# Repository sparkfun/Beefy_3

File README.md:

SparkFun FTDI Basic Breakout Board-3.3V
========================================

[*SparkFun Beefy 3 (3.3V FTDI Breakout) (DEV-13746)*](https://www.sparkfun.com/products/13746)

This is a breakout board for the FTDI FT232RL USB to serial IC with integrated 3.3V (up to 600mA) regulator to power your project.
The pinout of this board matches the FTDI cable to work with official Arduino and cloned 3.3V Arduino boards.

Repository Contents
-------------------
* **/Hardware** &mdash; All Eagle design files (.brd, .sch)
* **/Production** &mdash; Test bed files and production panel files

Product Versions
----------------
* 
[This](https://www.sparkfun.com/products/13746) &mdash; Higher power 3.3V FTDI Breakout.
* [DEV-09873](https://www.sparkfun.com/products/9873) &mdash; 3.3V FTDI Basic Breakout.
* [DEV-09716](https://www.sparkfun.com/products/9716) &mdash; 5V FTDI Basic Breakout

License Information
-------------------
The hardware is released under [Creative Commons ShareAlike 4.0 International](https://creativecommons.org/licenses/by-sa/4.0/).

Distributed as-is; no warranty is given.

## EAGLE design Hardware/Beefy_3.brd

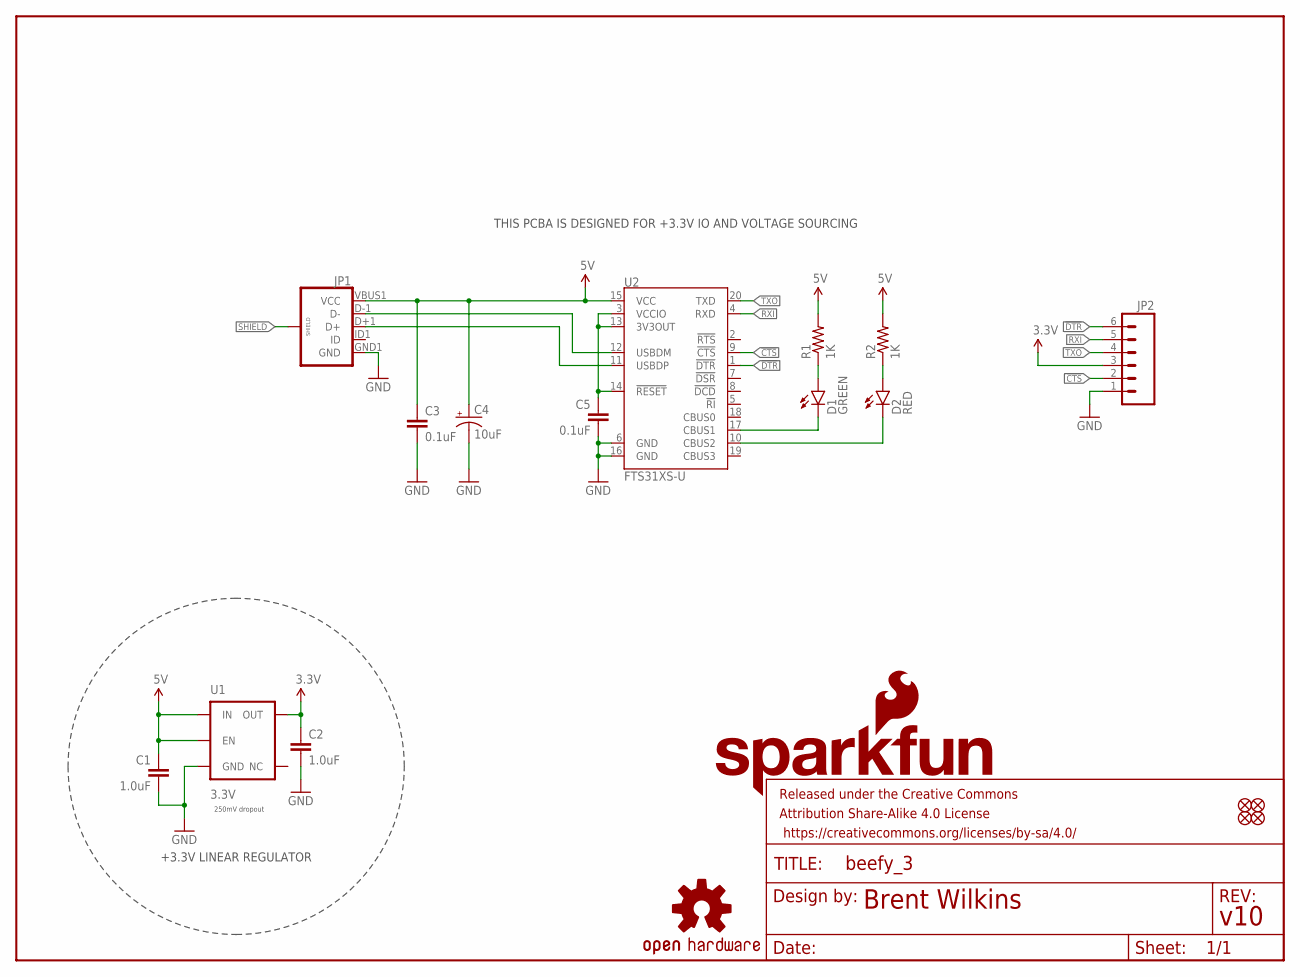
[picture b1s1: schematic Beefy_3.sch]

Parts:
C1, C2: 1.0uF; 0603-CAP
C3, C5: 0.1uF; 0603-CAP
C4: 10uF; EIA3216
D1: GREEN; LED-0603
D2: RED; LED-0603
FRAME1: FRAME-LETTER; CREATIVE_COMMONS
JP1: USB_MICROB_PLUGCONN-11752; USB-B-MICRO-SMD_V03
JP2: M06SMD-FEMALE-V2; 1X06-SMD-FEMALE-V2
JP3, JP4, JP5, JP6: FIDUCIAL1X2; FIDUCIAL-1X2
LOGO1: OSHW-LOGOS; OSHW-LOGO-S
LOGO2: SFE_LOGO_NAME.1_INCH; SFE_LOGO_NAME_.1
LOGO3: SFE_LOGO_FLAME.1_INCH; SFE_LOGO_FLAME_.1
R1, R2: 1K; 0603-RES
U1: 3.3V; SOT23-5
U2: FTS31XS-U; SSOP20_L

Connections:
3V3: C2.1, JP2.3, U1.5 (OUT)
3V3LC: C5.1, U2.3 (VCCIO), U2.13 (3V3OUT), U2.14 (!RESET)
5V: C1.1, C3.1, C4.A (+), JP1.VBUS1 (VCC), R1.2, R2.2, U1.1 (IN), U1.3 (EN), U2.15 (VCC)
!CTS: JP2.2, U2.9 (!CTS)
!DTR: JP2.6, U2.1 (!DTR)
GND: C1.2, C2.2, C3.2, C4.C (-), C5.2, JP1.GND1 (GND), JP2.1, U1.2 (GND), U2.6 (GND), U2.16 (GND)
unnamed: D2.A, R2.1
unnamed: D1.A, R1.1
RXI: JP2.5, U2.4 (RXD)
RXLED: D1.C, U2.17 (CBUS1)
SHIELD: JP1.SHIELD1 (SHIELD), JP1.SHIELD2 (SHIELD), JP1.SHIELD3 (SHIELD)
TXLED: D2.C, U2.10 (CBUS2)
TXO: JP2.4, U2.20 (TXD)
USB_D+: JP1.D+1 (D+), U2.11 (USBDP)
USB_D-: JP1.D-1 (D-), U2.12 (USBDM)

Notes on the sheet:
+3.3V LINEAR REGULATOR
250mV dropout
THIS PCBA IS DESIGNED FOR +3.3V IO AND VOLTAGE SOURCING

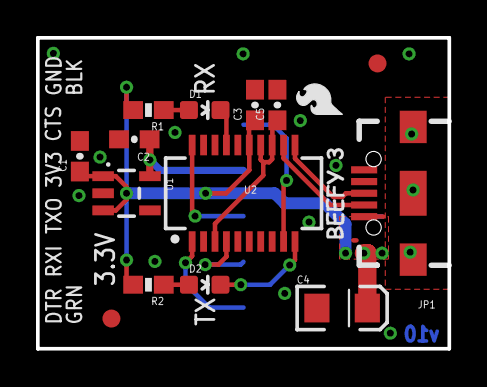
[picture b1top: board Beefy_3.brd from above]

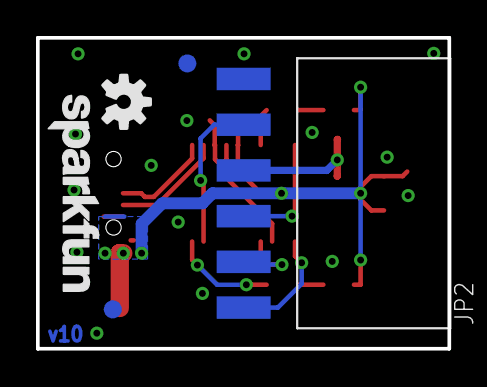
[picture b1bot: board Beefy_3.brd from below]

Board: 2 copper layers, 22.9 x 17.3 mm, 21 parts (5 on the bottom side), 15 nets.

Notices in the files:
parts and their libraries:
SparkFun-Aesthetics: Licensing: CC v3.0 Share-Alike You are welcome to use this library for commercial purposes.
SparkFun-Aesthetics: Released under the Creative Commons Attribution Share-Alike 4.0 License
SparkFun-Aesthetics: Released under the Creative Commons
